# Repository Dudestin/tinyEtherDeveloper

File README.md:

View this project on [CADLAB.io](https://cadlab.io/project/25780). 
Contact : [@mozc_channel](https://twitter.com/mozc_channel)

# [WIP]tinyEtherDeveloper
Inexpensive FPGA board-based Ethernet evaluation board project.  
Consists mostly of DIP components and uses Tang PriMER. It can be built for about only $50.

## About
**7,000円程度**でほとんどの部品が秋葉原で揃う, Ethernetポートを**4つ**備えた実験ボードです. 10BASE-Tに対応しています.  
はんだ付けが苦手な方でも容易に実装できるよう, 極力面実装部品の仕様は控えています.  
FPGAボードには, SipeedのTang PriMERを用いており, そこそこ豊富なBRAMを備えるため, 様々な応用が可能です.

| Overview | Overview2 | PCB Layout |
| --- | --- |  --- |
|  |  | |
## Usages and Applications
- Repeater Hub
- Video Broadcasting (Use with MIPI Camera)
- NTP Server
- L2 Switch
- L3 Switch
- Hardware VPN router

## Where to get parts
[部品表](https://partscabi.net/list/92284b79-cc50-4855-a5a0-e0b6e620e11a), [RTL8201CP](https://jp.rs-online.com/web/p/ethernet-interface-ics/0419952) (PHYチップ)

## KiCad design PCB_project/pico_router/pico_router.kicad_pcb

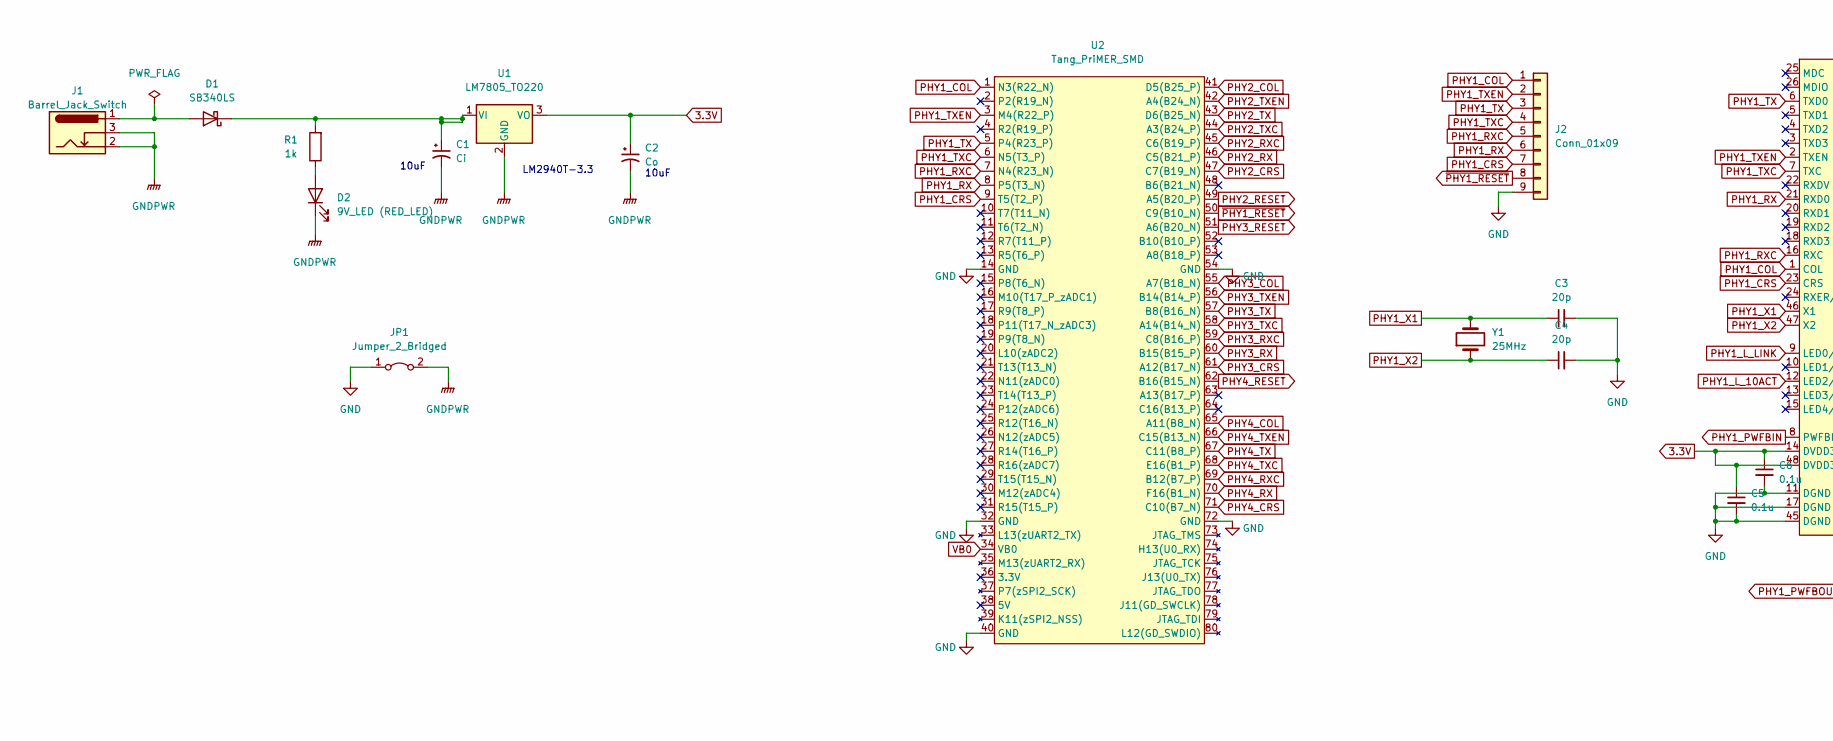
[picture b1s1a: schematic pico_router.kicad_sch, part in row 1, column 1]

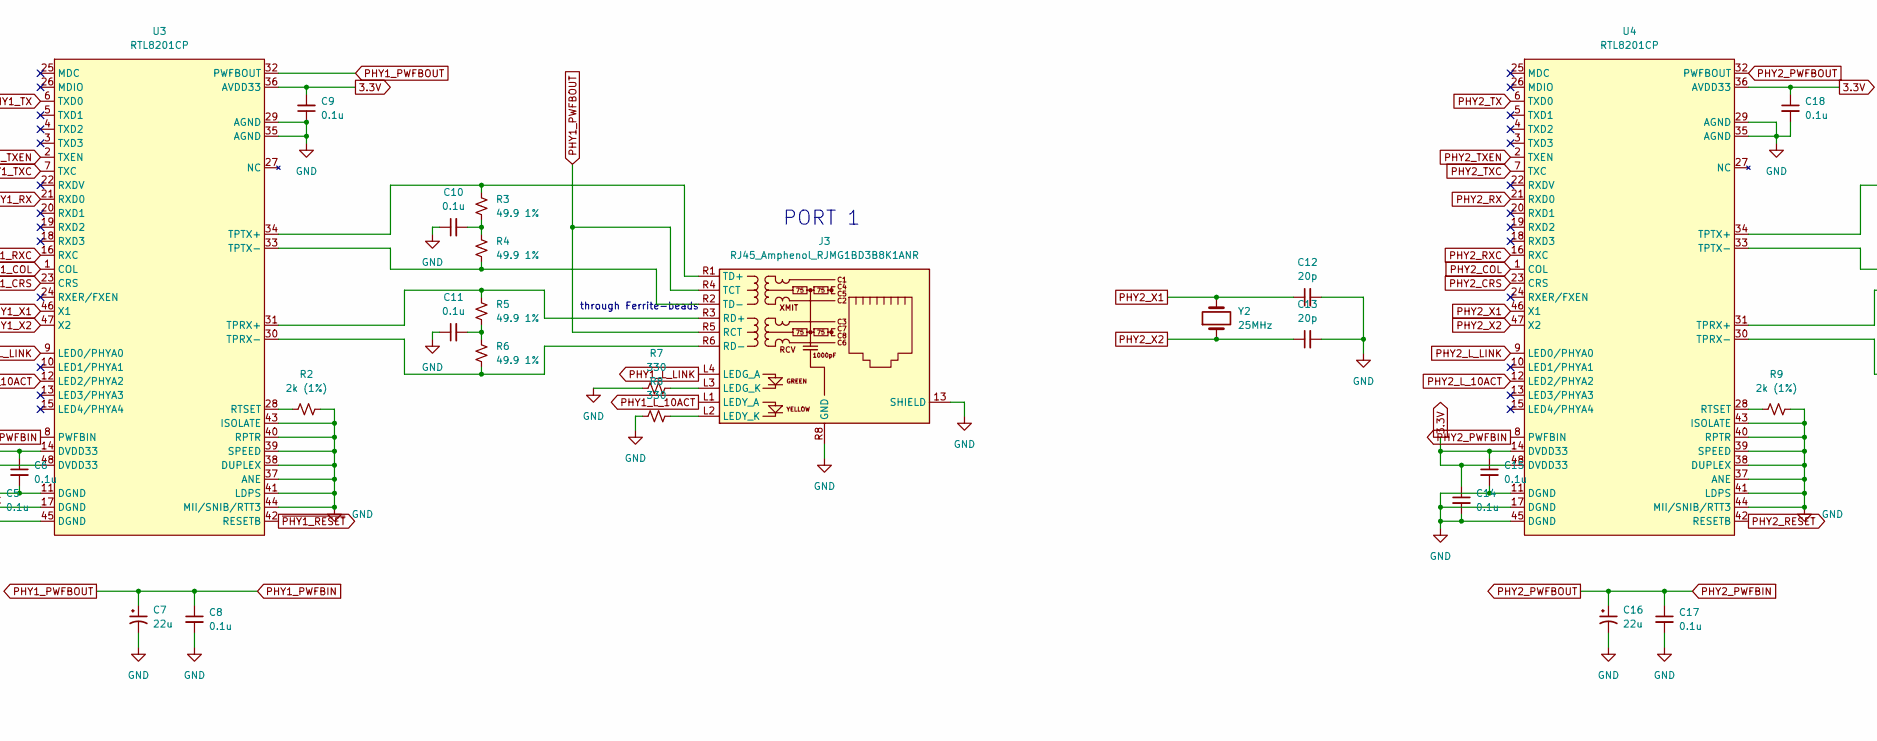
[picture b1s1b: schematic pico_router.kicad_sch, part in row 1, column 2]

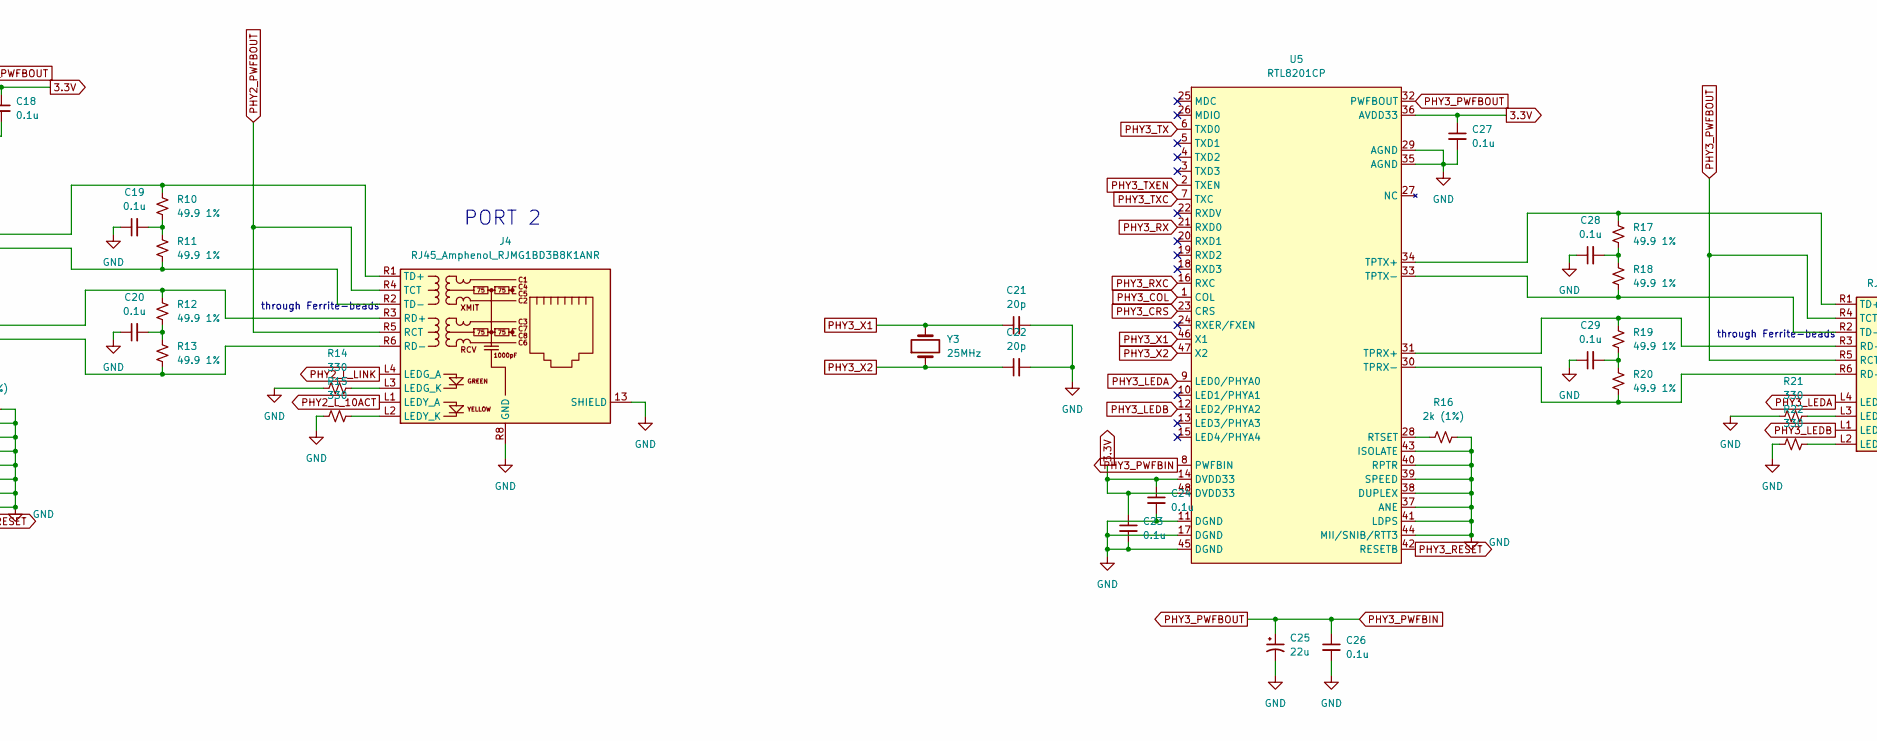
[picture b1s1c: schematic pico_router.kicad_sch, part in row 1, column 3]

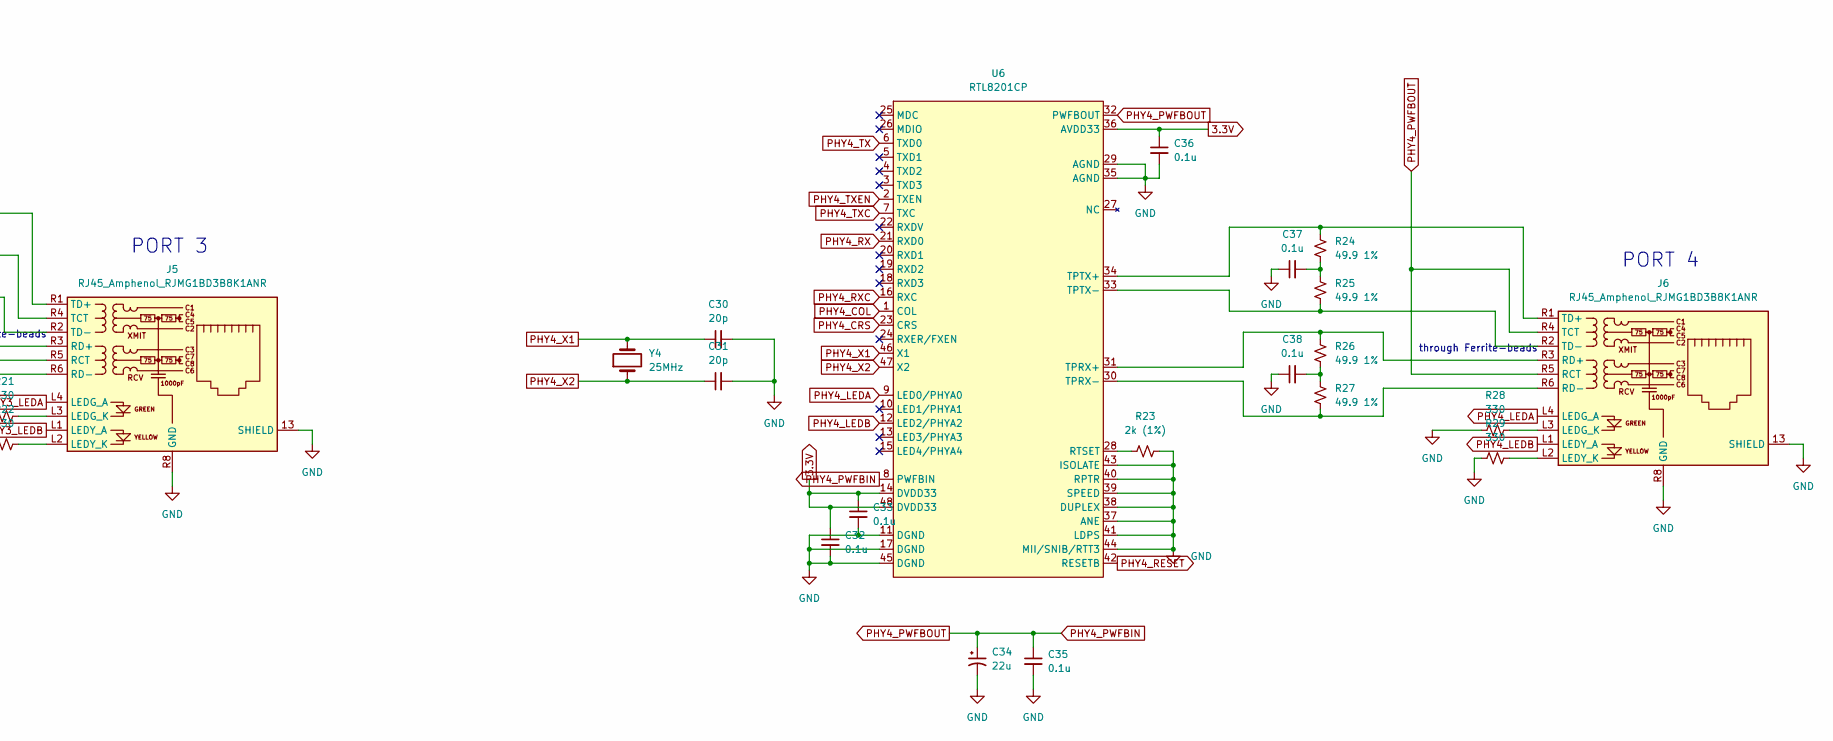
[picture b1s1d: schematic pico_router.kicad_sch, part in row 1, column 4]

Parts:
C1: Ci; CP_Radial_D4.0mm_P2.00mm
C2: Co; CP_Radial_D4.0mm_P2.00mm
C3, C4, C12, C13, C21, C22, C30, C31: 20p; C_Disc_D3.0mm_W1.6mm_P2.50mm
C5, C6, C8, C9, C10, C11, C14, C15, C17, C18, C19, C20, C23, C24, C26, C27, C28, C29, C32, C33, C35, C36, C37, C38: 0.1u; C_Disc_D3.0mm_W1.6mm_P2.50mm
C7, C16, C25, C34: 22u; CP_Radial_D5.0mm_P2.50mm
D1: SB340LS; D_DO-15_P10.16mm_Horizontal
D2: 9V_LED (RED_LED); LED_D3.0mm
J1: Barrel_Jack_Switch; BarrelJack_GCT_DCJ200-10-A_Horizontal
J2: Conn_01x09; PinHeader_1x09_P2.54mm_Vertical
J3, J4, J5, J6: RJ45_Amphenol_RJMG1BD3B8K1ANR
JP1: Jumper_2_Bridged; SolderJumper-2_P1.3mm_Bridged2Bar_RoundedPad1.0x1.5mm
R1: 1k; R_Axial_DIN0204_L3.6mm_D1.6mm_P5.08mm_Horizontal
R2, R9, R16, R23: 2k (1%); R_Axial_DIN0204_L3.6mm_D1.6mm_P1.90mm_Vertical
R3, R4, R5, R6, R10, R11, R12, R13, R17, R18, R19, R20, R24, R25, R26, R27: 49.9 1%; R_Axial_DIN0204_L3.6mm_D1.6mm_P5.08mm_Horizontal
R7, R8, R14, R15, R21, R22, R28, R29: 330; R_Axial_DIN0204_L3.6mm_D1.6mm_P5.08mm_Horizontal
U1: LM7805_TO220; TO-220-3_Vertical
U2: Tang_PriMER_SMD
U3, U4, U5, U6: RTL8201CP; LQFP-48_7x7mm_P0.5mm
Y1, Y2, Y3, Y4: 25MHz; Crystal_HC50_Vertical

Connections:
3.3V: C2.1, C5.1, C6.1, C9.2, C14.1, C15.1, C18.1, C23.1, C24.1, C27.1, C32.1, C33.1, C36.1, U1.3 (VO), U3.14 (DVDD33), U3.36 (AVDD33), U3.48 (DVDD33), U4.14 (DVDD33), U4.36 (AVDD33), U4.48 (DVDD33), U5.14 (DVDD33), U5.36 (AVDD33), U5.48 (DVDD33), U6.14 (DVDD33), U6.36 (AVDD33), U6.48 (DVDD33)
GND: C3.2, C4.2, C5.2, C6.2, C7.2, C8.2, C9.1, C10.1, C11.1, C12.2, C13.2, C14.2, C15.2, C16.2, C17.2, C18.2, C19.1, C20.1, C21.2, C22.2, C23.2, C24.2, C25.2, C26.2, C27.2, C28.1, C29.1, C30.2, C31.2, C32.2, C33.2, C34.2, C35.2, C36.2, C37.1, C38.1, J2.9, J3.13 (SHIELD), J3.R8 (GND), J4.13 (SHIELD), J4.R8 (GND), J5.13 (SHIELD), J5.R8 (GND), J6.13 (SHIELD), J6.R8 (GND), JP1.1 (A), R2.2, R7.1, R8.1, R9.2, R14.1, R15.1, R16.2, R21.1, R22.1, R23.2, R28.1, R29.1, U2.14 (GND), U2.32 (GND), U2.40 (GND), U2.54 (GND), U2.72 (GND), U3.11 (DGND), U3.17 (DGND), U3.29 (AGND), U3.35 (AGND), U3.37 (ANE), U3.38 (DUPLEX), U3.39 (SPEED), U3.40 (RPTR), U3.41 (LDPS), U3.43 (ISOLATE), U3.44 (MII/SNIB/RTT3), U3.45 (DGND), U4.11 (DGND), U4.17 (DGND), U4.29 (AGND), U4.35 (AGND), U4.37 (ANE), U4.38 (DUPLEX), U4.39 (SPEED), U4.40 (RPTR), U4.41 (LDPS), U4.43 (ISOLATE), U4.44 (MII/SNIB/RTT3), U4.45 (DGND), U5.11 (DGND), U5.17 (DGND), U5.29 (AGND), U5.35 (AGND), U5.37 (ANE), U5.38 (DUPLEX), U5.39 (SPEED), U5.40 (RPTR), U5.41 (LDPS), U5.43 (ISOLATE), U5.44 (MII/SNIB/RTT3), U5.45 (DGND), U6.11 (DGND), U6.17 (DGND), U6.29 (AGND), U6.35 (AGND), U6.37 (ANE), U6.38 (DUPLEX), U6.39 (SPEED), U6.40 (RPTR), U6.41 (LDPS), U6.43 (ISOLATE), U6.44 (MII/SNIB/RTT3), U6.45 (DGND)
GNDPWR: C1.2, C2.2, D2.1 (K), J1.2, J1.3, JP1.2 (B), U1.2 (GND)
unnamed: C1.1, D1.1 (K), R1.2, U1.1 (VI)
unnamed: C10.2, R3.2, R4.1
unnamed: C11.2, R5.2, R6.1
unnamed: C19.2, R10.2, R11.1
unnamed: C20.2, R12.2, R13.1
unnamed: C28.2, R17.2, R18.1
unnamed: C29.2, R19.2, R20.1
unnamed: C37.2, R24.2, R25.1
unnamed: C38.2, R26.2, R27.1
unnamed: D1.2 (A), J1.1
unnamed: D2.2 (A), R1.1
unnamed: J3.L2 (LEDY_K), R8.2
unnamed: J3.L3 (LEDG_K), R7.2
unnamed: J3.R1 (TD+), R3.1, U3.34 (TPTX+)
unnamed: J3.R2 (TD-), R4.2, U3.33 (TPTX-)
unnamed: J3.R3 (RD+), R5.1, U3.31 (TPRX+)
unnamed: J3.R6 (RD-), R6.2, U3.30 (TPRX-)
unnamed: J4.L2 (LEDY_K), R15.2
unnamed: J4.L3 (LEDG_K), R14.2
unnamed: J4.R1 (TD+), R10.1, U4.34 (TPTX+)
unnamed: J4.R2 (TD-), R11.2, U4.33 (TPTX-)
unnamed: J4.R3 (RD+), R12.1, U4.31 (TPRX+)
unnamed: J4.R6 (RD-), R13.2, U4.30 (TPRX-)
unnamed: J5.L2 (LEDY_K), R22.2
unnamed: J5.L3 (LEDG_K), R21.2
unnamed: J5.R1 (TD+), R17.1, U5.34 (TPTX+)
unnamed: J5.R2 (TD-), R18.2, U5.33 (TPTX-)
unnamed: J5.R3 (RD+), R19.1, U5.31 (TPRX+)
unnamed: J5.R6 (RD-), R20.2, U5.30 (TPRX-)
unnamed: J6.L2 (LEDY_K), R29.2
unnamed: J6.L3 (LEDG_K), R28.2
unnamed: J6.R1 (TD+), R24.1, U6.34 (TPTX+)
unnamed: J6.R2 (TD-), R25.2, U6.33 (TPTX-)
unnamed: J6.R3 (RD+), R26.1, U6.31 (TPRX+)
unnamed: J6.R6 (RD-), R27.2, U6.30 (TPRX-)
unnamed: R2.1, U3.28 (RTSET)
unnamed: R9.1, U4.28 (RTSET)
unnamed: R16.1, U5.28 (RTSET)
unnamed: R23.1, U6.28 (RTSET)
PHY1_COL: J2.1, U2.1 (N3(R22_N)), U3.1 (COL)
PHY1_CRS: J2.7, U2.9 (T5(T2_P)), U3.23 (CRS)
PHY1_L_10ACT: J3.L1 (LEDY_A), U3.12 (LED2/PHYA2)
PHY1_L_LINK: J3.L4 (LEDG_A), U3.9 (LED0/PHYA0)
PHY1_PWFBIN: C7.1, C8.1, J3.R4 (TCT), J3.R5 (RCT), U3.8 (PWFBIN), U3.32 (PWFBOUT)
PHY1_RX: J2.6, U2.8 (P5(T3_N)), U3.21 (RXD0)
PHY1_RXC: J2.5, U2.7 (N4(R23_N)), U3.16 (RXC)
PHY1_TX: J2.3, U2.5 (P4(R23_P)), U3.6 (TXD0)
PHY1_TXC: J2.4, U2.6 (N5(T3_P)), U3.7 (TXC)
PHY1_TXEN: J2.2, U2.3 (M4(R22_P)), U3.2 (TXEN)
PHY1_X1: C3.1, U3.46 (X1), Y1.2
PHY1_X2: C4.1, U3.47 (X2), Y1.1
PHY2_COL: U2.41 (D5(B25_P)), U4.1 (COL)
PHY2_CRS: U2.47 (C7(B19_N)), U4.23 (CRS)
PHY2_L_10ACT: J4.L1 (LEDY_A), U4.12 (LED2/PHYA2)
PHY2_L_LINK: J4.L4 (LEDG_A), U4.9 (LED0/PHYA0)
PHY2_PWFBIN: C16.1, C17.1, J4.R4 (TCT), J4.R5 (RCT), U4.8 (PWFBIN), U4.32 (PWFBOUT)
PHY2_RESET: U2.49 (A5(B20_P)), U4.42 (RESETB)
PHY2_RX: U2.46 (C5(B21_P)), U4.21 (RXD0)
PHY2_RXC: U2.45 (C6(B19_P)), U4.16 (RXC)
PHY2_TX: U2.43 (D6(B25_N)), U4.6 (TXD0)
PHY2_TXC: U2.44 (A3(B24_P)), U4.7 (TXC)
PHY2_TXEN: U2.42 (A4(B24_N)), U4.2 (TXEN)
PHY2_X1: C12.1, U4.46 (X1), Y2.2
PHY2_X2: C13.1, U4.47 (X2), Y2.1
PHY3_COL: U2.55 (A7(B18_N)), U5.1 (COL)
PHY3_CRS: U2.61 (A12(B17_N)), U5.23 (CRS)
PHY3_LEDA: J5.L4 (LEDG_A), U5.9 (LED0/PHYA0)
PHY3_LEDB: J5.L1 (LEDY_A), U5.12 (LED2/PHYA2)
PHY3_PWFBIN: C25.1, C26.1, J5.R4 (TCT), J5.R5 (RCT), U5.8 (PWFBIN), U5.32 (PWFBOUT)
PHY3_RESET: U2.51 (A6(B20_N)), U5.42 (RESETB)
PHY3_RX: U2.60 (B15(B15_P)), U5.21 (RXD0)
PHY3_RXC: U2.59 (C8(B16_P)), U5.16 (RXC)
PHY3_TX: U2.57 (B8(B16_N)), U5.6 (TXD0)
PHY3_TXC: U2.58 (A14(B14_N)), U5.7 (TXC)
PHY3_TXEN: U2.56 (B14(B14_P)), U5.2 (TXEN)
PHY3_X1: C21.1, U5.46 (X1), Y3.2
PHY3_X2: C22.1, U5.47 (X2), Y3.1
PHY4_COL: U2.65 (A11(B8_N)), U6.1 (COL)
PHY4_CRS: U2.71 (C10(B7_N)), U6.23 (CRS)
PHY4_LEDA: J6.L4 (LEDG_A), U6.9 (LED0/PHYA0)
PHY4_LEDB: J6.L1 (LEDY_A), U6.12 (LED2/PHYA2)
PHY4_PWFBIN: C34.1, C35.1, J6.R4 (TCT), J6.R5 (RCT), U6.8 (PWFBIN), U6.32 (PWFBOUT)
PHY4_RESET: U2.62 (B16(B15_N)), U6.42 (RESETB)
PHY4_RX: U2.70 (F16(B1_N)), U6.21 (RXD0)
PHY4_RXC: U2.69 (B12(B7_P)), U6.16 (RXC)
PHY4_TX: U2.67 (C11(B8_P)), U6.6 (TXD0)
PHY4_TXC: U2.68 (E16(B1_P)), U6.7 (TXC)
PHY4_TXEN: U2.66 (C15(B13_N)), U6.2 (TXEN)
PHY4_X1: C30.1, U6.46 (X1), Y4.2
PHY4_X2: C31.1, U6.47 (X2), Y4.1
VB0: U2.34 (VB0)
~PHY1_RESET: J2.8, U2.50 (C9(B10_N)), U3.42 (RESETB)

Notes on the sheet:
PORT 2
LM2940T-3.3
PORT 4
through Ferrite-beads
PORT 1
10uF
PORT 3

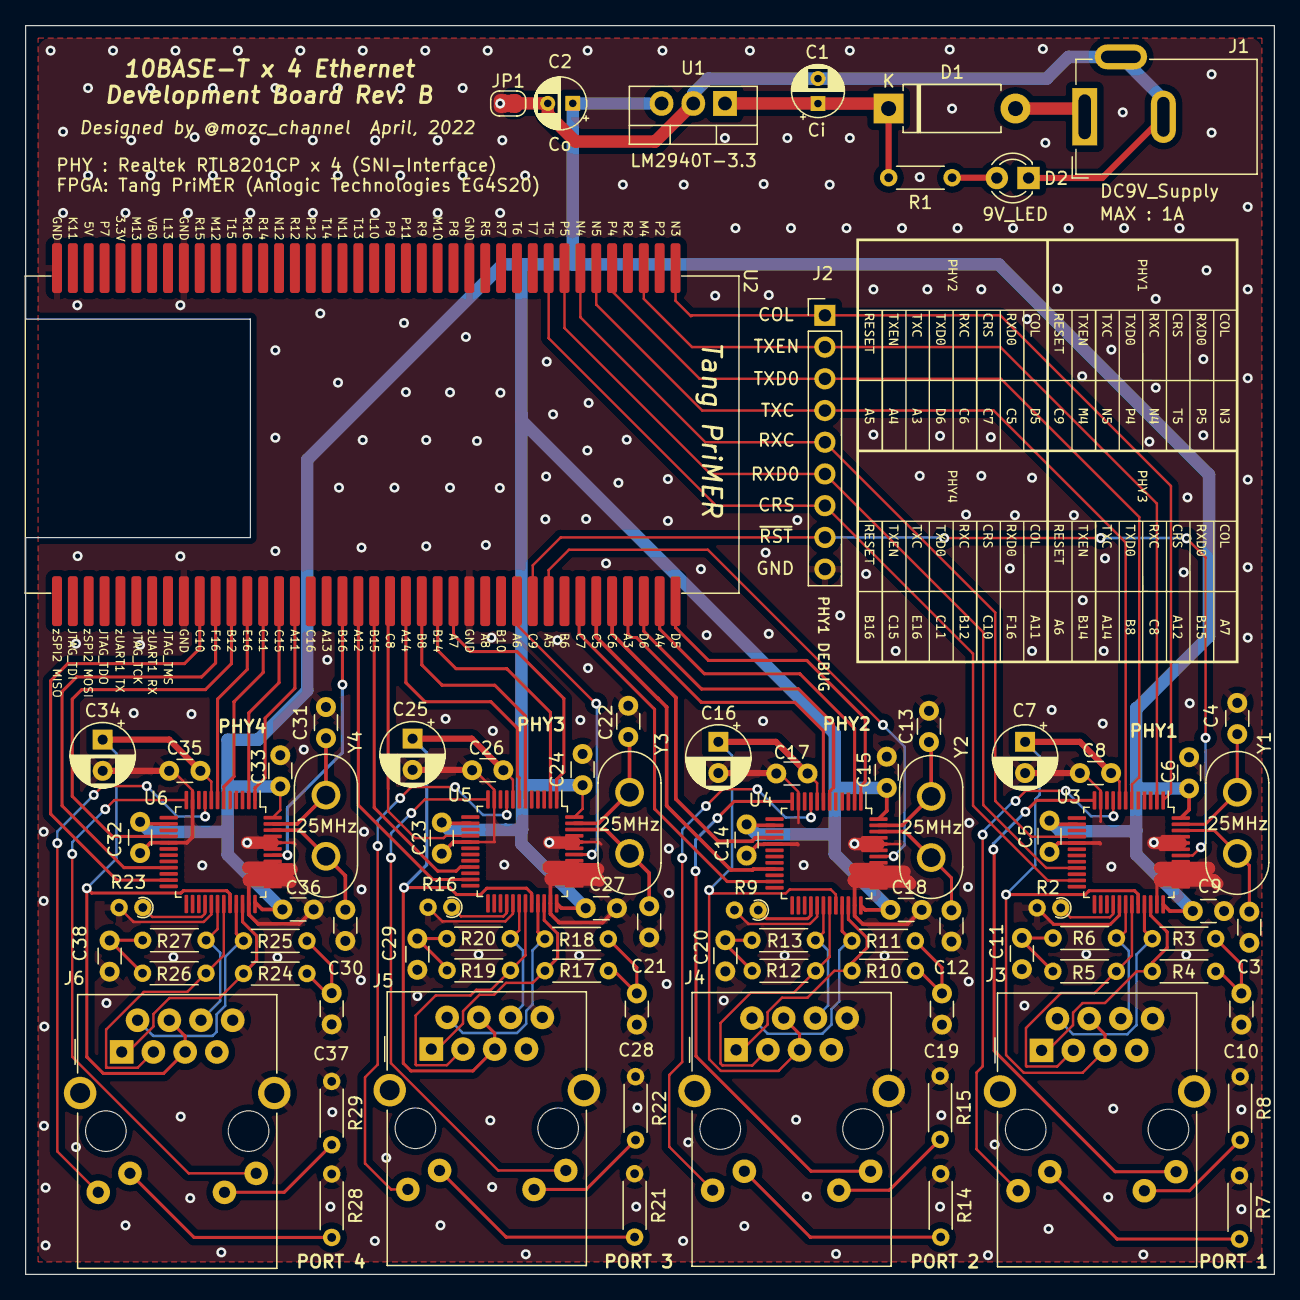
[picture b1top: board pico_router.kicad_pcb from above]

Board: 2 copper layers, 100.0 x 100.0 mm, 86 parts (0 on the bottom side), 94 nets.

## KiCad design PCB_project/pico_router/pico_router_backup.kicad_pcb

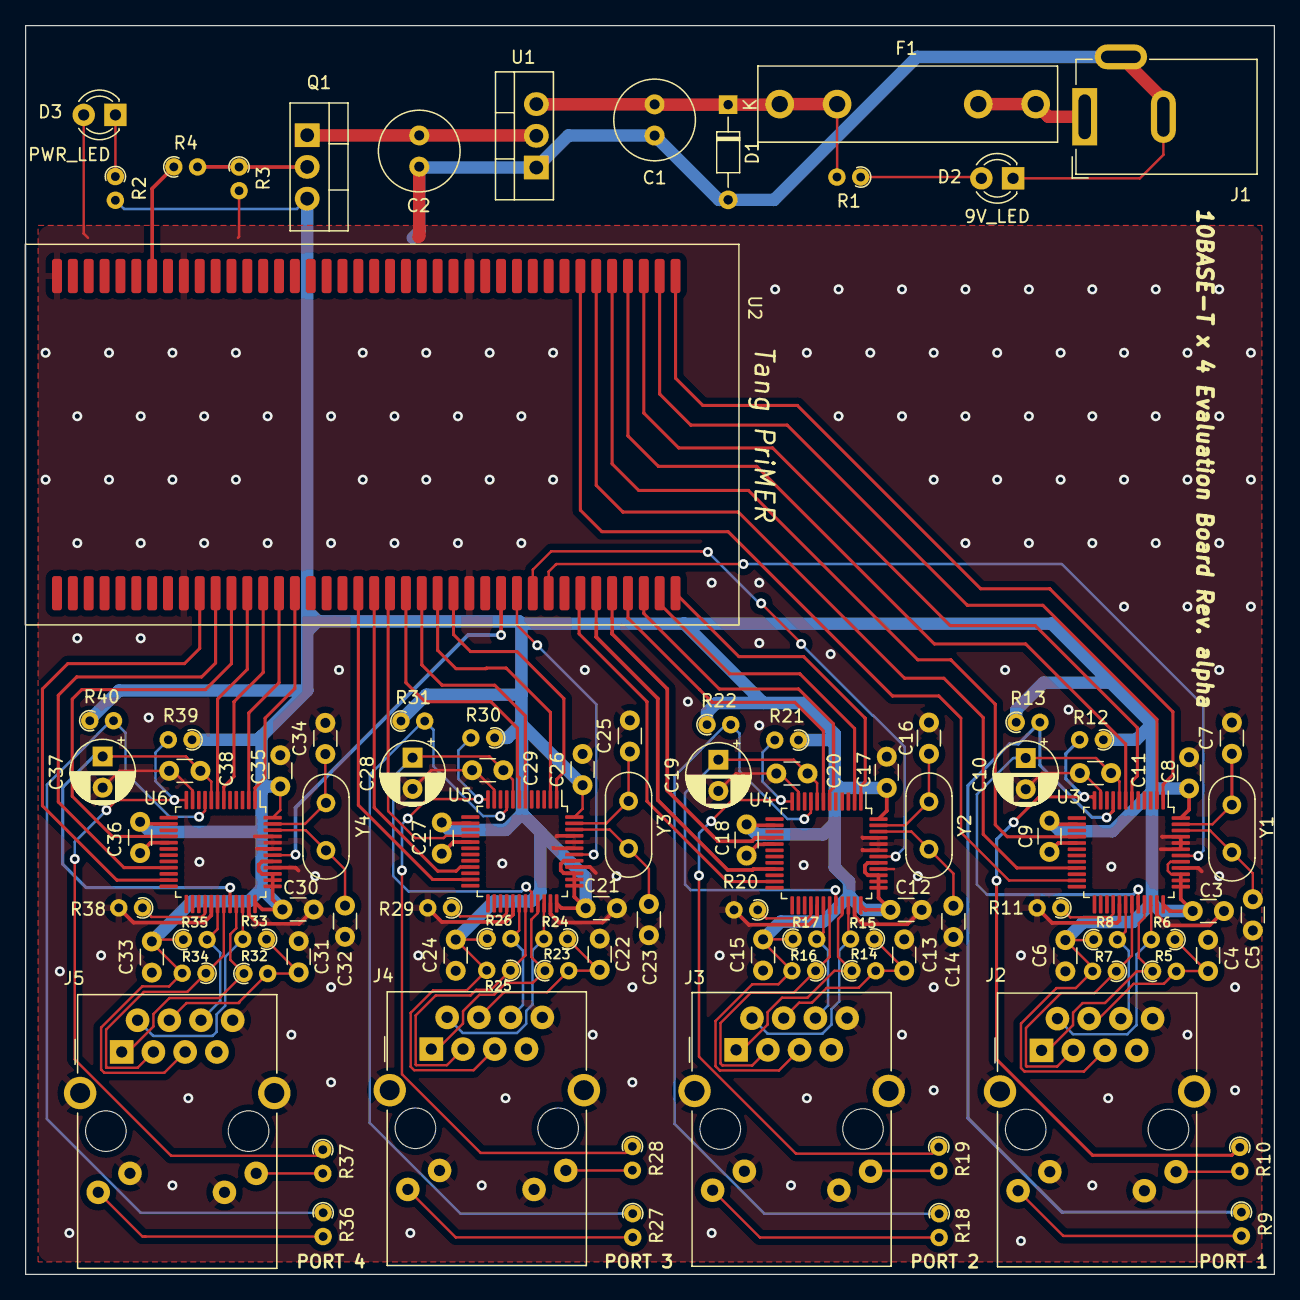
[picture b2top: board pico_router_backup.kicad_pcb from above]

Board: 2 copper layers, 100.0 x 100.0 mm, 98 parts (0 on the bottom side), 93 nets.

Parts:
C1: Ci; C_Radial_D6.3mm_H11.0mm_P2.50mm
C2: Co; C_Radial_D6.3mm_H11.0mm_P2.50mm
C3, C4, C6, C8, C9, C11, C12, C13, C15, C17, C18, C20, C21, C22, C24, C26, C27, C29, C30, C31, C33, C35, C36, C38: 0.1u; C_Disc_D3.0mm_W1.6mm_P2.50mm
C5, C7, C14, C16, C23, C25, C32, C34: 20p; C_Disc_D3.0mm_W1.6mm_P2.50mm
C10, C19, C28, C37: 22u; CP_Radial_D5.0mm_P2.50mm
D1: 9.1V; D_DO-34_SOD68_P7.62mm_Horizontal
D2: 9V_LED (RED_LED); LED_D3.0mm
D3: PWR_LED (BLUE); LED_D3.0mm
F1: 1A; Fuseholder_Littelfuse_100_series_5x20mm
J1: Barrel_Jack_Switch; BarrelJack_GCT_DCJ200-10-A_Horizontal
J2, J3, J4, J5: RJ45_Amphenol_RJMG1BD3B8K1ANR
Q1: 2SK4017; TO-220-3_Vertical
R1: 1k; R_Axial_DIN0204_L3.6mm_D1.6mm_P1.90mm_Vertical
R2, R4, R9, R10, R18, R19, R27, R28, R36, R37: 330; R_Axial_DIN0204_L3.6mm_D1.6mm_P1.90mm_Vertical
R3: 10k; R_Axial_DIN0204_L3.6mm_D1.6mm_P1.90mm_Vertical
R5, R6, R7, R8, R14, R15, R16, R17, R23, R24, R25, R26, R32, R33, R34, R35: 49.9 1%; R_Axial_DIN0204_L3.6mm_D1.6mm_P1.90mm_Vertical
R11, R20, R29, R38: 2k (1%); R_Axial_DIN0204_L3.6mm_D1.6mm_P1.90mm_Vertical
R12, R13, R21, R22, R30, R31, R39, R40: 5.1k; R_Axial_DIN0204_L3.6mm_D1.6mm_P1.90mm_Vertical
U1: LM317_TO-220; TO-220-3_Vertical
U2: Tang_PriMER_SMD
U3, U4, U5, U6: RTL8201CP; LQFP-48_7x7mm_P0.5mm
Y1, Y2, Y3, Y4: 25MHz; Crystal_HC52-6mm_Vertical

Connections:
3.3V: C3.1, C6.2, C8.1, C9.1, C12.1, C15.2, C17.1, C18.1, C21.1, C24.2, C26.1, C27.1, C30.1, C33.2, C35.1, C36.1, J2.R5 (RCT), J3.R5 (RCT), J4.R5 (RCT), J5.R5 (RCT), Q1.3 (S), R2.2, R7.2, R8.1, R12.1, R13.1, R16.2, R17.1, R21.1, R22.1, R25.2, R26.1, R30.1, R31.1, R34.2, R35.1, R39.1, R40.1, U3.14 (DVDD33), U3.36 (AVDD33), U3.37 (ANE), U3.38 (DUPLEX), U3.39 (SPEED), U3.41 (LDPS), U3.48 (DVDD33), U4.14 (DVDD33), U4.36 (AVDD33), U4.37 (ANE), U4.38 (DUPLEX), U4.39 (SPEED), U4.41 (LDPS), U4.48 (DVDD33), U5.14 (DVDD33), U5.36 (AVDD33), U5.37 (ANE), U5.38 (DUPLEX), U5.39 (SPEED), U5.41 (LDPS), U5.48 (DVDD33), U6.14 (DVDD33), U6.36 (AVDD33), U6.37 (ANE), U6.38 (DUPLEX), U6.39 (SPEED), U6.41 (LDPS), U6.48 (DVDD33)
DC_OUT: C2.1, Q1.1 (D), U1.2 (VO)
GND: C1.2, C2.2, C3.2, C4.1, C5.2, C6.1, C7.2, C8.2, C9.2, C10.2, C11.2, C12.2, C13.1, C14.2, C15.1, C16.2, C17.2, C18.2, C19.2, C20.2, C21.2, C22.1, C23.2, C24.1, C25.2, C26.2, C27.2, C28.2, C29.2, C30.2, C31.1, C32.2, C33.1, C34.2, C35.2, C36.2, C37.2, C38.2, D1.2 (A), D2.1 (K), D3.2 (A), J1.2, J1.3, J2.13 (SHIELD), J2.L2 (LEDY_K), J2.L3 (LEDG_K), J2.R8 (GND), J3.13 (SHIELD), J3.L2 (LEDY_K), J3.L3 (LEDG_K), J3.R8 (GND), J4.13 (SHIELD), J4.L2 (LEDY_K), J4.L3 (LEDG_K), J4.R8 (GND), J5.13 (SHIELD), J5.L2 (LEDY_K), J5.L3 (LEDG_K), J5.R8 (GND), R3.2, R11.2, R20.2, R29.2, R38.2, U1.1 (ADJ), U2.14 (GND), U2.32 (GND), U2.40 (GND), U2.54 (GND), U2.72 (GND), U3.11 (DGND), U3.17 (DGND), U3.29 (AGND), U3.35 (AGND), U3.40 (RPTR), U3.43 (ISOLATE), U3.44 (MII/SNIB/RTT3), U3.45 (DGND), U4.11 (DGND), U4.17 (DGND), U4.29 (AGND), U4.35 (AGND), U4.40 (RPTR), U4.43 (ISOLATE), U4.44 (MII/SNIB/RTT3), U4.45 (DGND), U5.11 (DGND), U5.17 (DGND), U5.29 (AGND), U5.35 (AGND), U5.40 (RPTR), U5.43 (ISOLATE), U5.44 (MII/SNIB/RTT3), U5.45 (DGND), U6.11 (DGND), U6.17 (DGND), U6.29 (AGND), U6.35 (AGND), U6.40 (RPTR), U6.43 (ISOLATE), U6.44 (MII/SNIB/RTT3), U6.45 (DGND)
unnamed: C1.1, D1.1 (K), F1.1, R1.2, U1.3 (VI)
unnamed: C4.2, J2.R4 (TCT), R5.2, R6.1
unnamed: C13.2, J3.R4 (TCT), R14.2, R15.1
unnamed: C22.2, J4.R4 (TCT), R23.2, R24.1
unnamed: C31.2, J5.R4 (TCT), R32.2, R33.1
unnamed: D2.2 (A), R1.1
unnamed: D3.1 (K), R2.1
unnamed: F1.2, J1.1
unnamed: J2.L1 (LEDY_A), R10.2
unnamed: J2.L4 (LEDG_A), R9.2
unnamed: J2.R1 (TD+), R5.1, U3.33 (TPTX+)
unnamed: J2.R2 (TD-), R6.2, U3.34 (TPTX-)
unnamed: J2.R3 (RD+), R7.1, U3.31 (TPRX+)
unnamed: J2.R6 (RD-), R8.2, U3.30 (TPRX-)
unnamed: J3.L1 (LEDY_A), R19.2
unnamed: J3.L4 (LEDG_A), R18.2
unnamed: J3.R1 (TD+), R14.1, U4.33 (TPTX+)
unnamed: J3.R2 (TD-), R15.2, U4.34 (TPTX-)
unnamed: J3.R3 (RD+), R16.1, U4.31 (TPRX+)
unnamed: J3.R6 (RD-), R17.2, U4.30 (TPRX-)
unnamed: J4.L1 (LEDY_A), R28.2
unnamed: J4.L4 (LEDG_A), R27.2
unnamed: J4.R1 (TD+), R23.1, U5.33 (TPTX+)
unnamed: J4.R2 (TD-), R24.2, U5.34 (TPTX-)
unnamed: J4.R3 (RD+), R25.1, U5.31 (TPRX+)
unnamed: J4.R6 (RD-), R26.2, U5.30 (TPRX-)
unnamed: J5.L1 (LEDY_A), R37.2
unnamed: J5.L4 (LEDG_A), R36.2
unnamed: J5.R1 (TD+), R32.1, U6.33 (TPTX+)
unnamed: J5.R2 (TD-), R33.2, U6.34 (TPTX-)
unnamed: J5.R3 (RD+), R34.1, U6.31 (TPRX+)
unnamed: J5.R6 (RD-), R35.2, U6.30 (TPRX-)
unnamed: Q1.2 (G), R3.1, R4.2
unnamed: R11.1, U3.28 (RTSET)
unnamed: R20.1, U4.28 (RTSET)
unnamed: R29.1, U5.28 (RTSET)
unnamed: R38.1, U6.28 (RTSET)
PHY1_COL: U2.1 (N3(R22_N)), U3.1 (COL)
PHY1_CRS: U2.7 (N4(R23_N)), U3.23 (CRS)
PHY1_LEDA: R9.1, R13.2, U3.9 (LED0/PHYA0)
PHY1_LEDB: R10.1, R12.2, U3.12 (LED2/PHYA2)
PHY1_PWFBIN: C10.1, C11.1, U3.8 (PWFBIN), U3.32 (PWFBOUT)
PHY1_RESET: U2.49 (A5(B20_P)), U3.42 (RESETB)
PHY1_RX: U2.6 (N5(T3_P)), U3.21 (RXD0)
PHY1_RXC: U2.5 (P4(R23_P)), U3.16 (RXC)
PHY1_TX: U2.3 (M4(R22_P)), U3.6 (TXD0)
PHY1_TXC: U2.4 (R2(R19_P)), U3.7 (TXC)
PHY1_TXEN: U2.2 (P2(R19_N)), U3.2 (TXEN)
PHY1_X1: C5.1, U3.46 (X1), Y1.2
PHY1_X2: C7.1, U3.47 (X2), Y1.1
PHY2_COL: U2.41 (D5(B25_P)), U4.1 (COL)
PHY2_CRS: U2.47 (C7(B19_N)), U4.23 (CRS)
PHY2_LEDA: R18.1, R22.2, U4.9 (LED0/PHYA0)
PHY2_LEDB: R19.1, R21.2, U4.12 (LED2/PHYA2)
PHY2_PWFBIN: C19.1, C20.1, U4.8 (PWFBIN), U4.32 (PWFBOUT)
PHY2_RESET: U2.50 (C9(B10_N)), U4.42 (RESETB)
PHY2_RX: U2.46 (C5(B21_P)), U4.21 (RXD0)
PHY2_RXC: U2.45 (C6(B19_P)), U4.16 (RXC)
PHY2_TX: U2.43 (D6(B25_N)), U4.6 (TXD0)
PHY2_TXC: U2.44 (A3(B24_P)), U4.7 (TXC)
PHY2_TXEN: U2.42 (A4(B24_N)), U4.2 (TXEN)
PHY2_X1: C14.1, U4.46 (X1), Y2.2
PHY2_X2: C16.1, U4.47 (X2), Y2.1
PHY3_COL: U2.55 (A7(B18_N)), U5.1 (COL)
PHY3_CRS: U2.61 (A12(B17_N)), U5.23 (CRS)
PHY3_LEDA: R27.1, R31.2, U5.9 (LED0/PHYA0)
PHY3_LEDB: R28.1, R30.2, U5.12 (LED2/PHYA2)
PHY3_PWFBIN: C28.1, C29.1, U5.8 (PWFBIN), U5.32 (PWFBOUT)
PHY3_RESET: U2.51 (A6(B20_N)), U5.42 (RESETB)
PHY3_RX: U2.60 (B15(B15_P)), U5.21 (RXD0)
PHY3_RXC: U2.59 (C8(B16_P)), U5.16 (RXC)
PHY3_TX: U2.57 (B8(B16_N)), U5.6 (TXD0)
PHY3_TXC: U2.58 (A14(B14_N)), U5.7 (TXC)
PHY3_TXEN: U2.56 (B14(B14_P)), U5.2 (TXEN)
PHY3_X1: C23.1, U5.46 (X1), Y3.2
PHY3_X2: C25.1, U5.47 (X2), Y3.1
PHY4_COL: U2.65 (A11(B8_N)), U6.1 (COL)
PHY4_CRS: U2.71 (C10(B7_N)), U6.23 (CRS)
PHY4_LEDA: R36.1, R40.2, U6.9 (LED0/PHYA0)
PHY4_LEDB: R37.1, R39.2, U6.12 (LED2/PHYA2)
PHY4_PWFBIN: C37.1, C38.1, U6.8 (PWFBIN), U6.32 (PWFBOUT)
PHY4_RESET: U2.52 (B10(B10_P)), U6.42 (RESETB)
PHY4_RX: U2.70 (F16(B1_N)), U6.21 (RXD0)
PHY4_RXC: U2.69 (B12(B7_P)), U6.16 (RXC)
PHY4_TX: U2.67 (C11(B8_P)), U6.6 (TXD0)
PHY4_TXC: U2.68 (E16(B1_P)), U6.7 (TXC)
PHY4_TXEN: U2.66 (C15(B13_N)), U6.2 (TXEN)
PHY4_X1: C32.1, U6.46 (X1), Y4.2
PHY4_X2: C34.1, U6.47 (X2), Y4.1
VB0: R4.1, U2.34 (VB0)

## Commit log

2022-07-07 change README.md location
2022-07-07 Backlink to CADLAB.io has been added.
2022-07-07 add PCB_project
2022-07-21 add MAC_DEC
2022-07-21 add verilog-cam@alexforencich under L2Switch/src
2022-07-23 CAMのBRAM実装のEG4S20への移植
2022-07-23 remove xorshift.v
2022-07-23 MAC_DEC.v 複数入力FIFO, 処理スケジューラの実装
2022-07-23 add MAC_SWITCH
2022-07-24 fix some bugs in MAC_DEC.v
2022-07-24 PHY_TX.vをリファクタリング
2022-07-25 FCSのチェック機能をMAC_DEC.vに実装
2022-07-25 add L2-Switch README.md
2022-07-25 add L2-switch top bench
2022-07-25 update io constraints
2022-07-25 check FCS valid section
2022-07-25 reset crc unit in S_FCS state
2022-07-25 file name change : HomemadeSwitch.al -> L2-Switch.al
2022-07-25 合成に成功
2022-07-25 fix DEMUX
2022-07-26 some fix after simulation
2022-08-11 fix some issue
2022-08-11 organize IP
2022-08-11 remove ASYNC_FIFO32k.v
2022-08-11 rename CTRL_FRAME_FIFO.v
2022-08-13 add Processr MAC interface
2022-08-13 fix, gray2bin to bin2gray
2022-08-13 add soc
2022-08-13 rename PHY -> SNI
2022-08-13 fix some bugs
2022-08-15 use stdint.h
2022-08-15 fix delimiter writing bugs
2022-08-15 rm backup files
2022-08-15 impl. hardware FCS calculation
2022-08-17 don't use priority encoder & delete backup files
2022-08-18 add synchronizer to afull flag
2022-08-18 impl. more sophisticate schedular
2022-08-18 validate FRAME_FIFO
2022-08-18 use active-low reset signal
2022-08-18 validate NEW_PACKET_FIFO
2022-08-18 validate RMII_TX.v
2022-08-18 fix bugs
2022-08-21 separate under FPGA dir.
2022-08-23 update RMII module
2022-08-23 fix IO constraints in Repeater
2022-08-23 add TD project file
2022-08-24 add frame_exist flag to FRAME_FIFO.v
2022-08-24 adapt MAC_DEC to fifo_exist flag
2022-08-24 remove match_signal, match_addr from cam module
2022-08-24 renew contraints & apply some fix on MAC_SWITCH
2022-08-25 fix RMII_TX coding style
2022-08-25 tab to space
2022-08-26 renew RMII_RX writing style
2022-08-26 fix FRAME_FIFO.v latency is incorrect
2022-08-26 fix FRAME_FIFO.v latency is invalid
2022-08-26 verify MAC_DEC.v
2022-08-26 add PACKET_FIFO IP ver.
2022-08-28 fix fix fix
2022-08-28 verify RTL SYNC FIFO
2022-08-28 use RTL FIFO and success to run
2022-08-30 downclock clock
2022-08-31 impl soc complete
2022-09-03 update MDIO
2022-09-03 firmware update
2022-09-03 fuga
